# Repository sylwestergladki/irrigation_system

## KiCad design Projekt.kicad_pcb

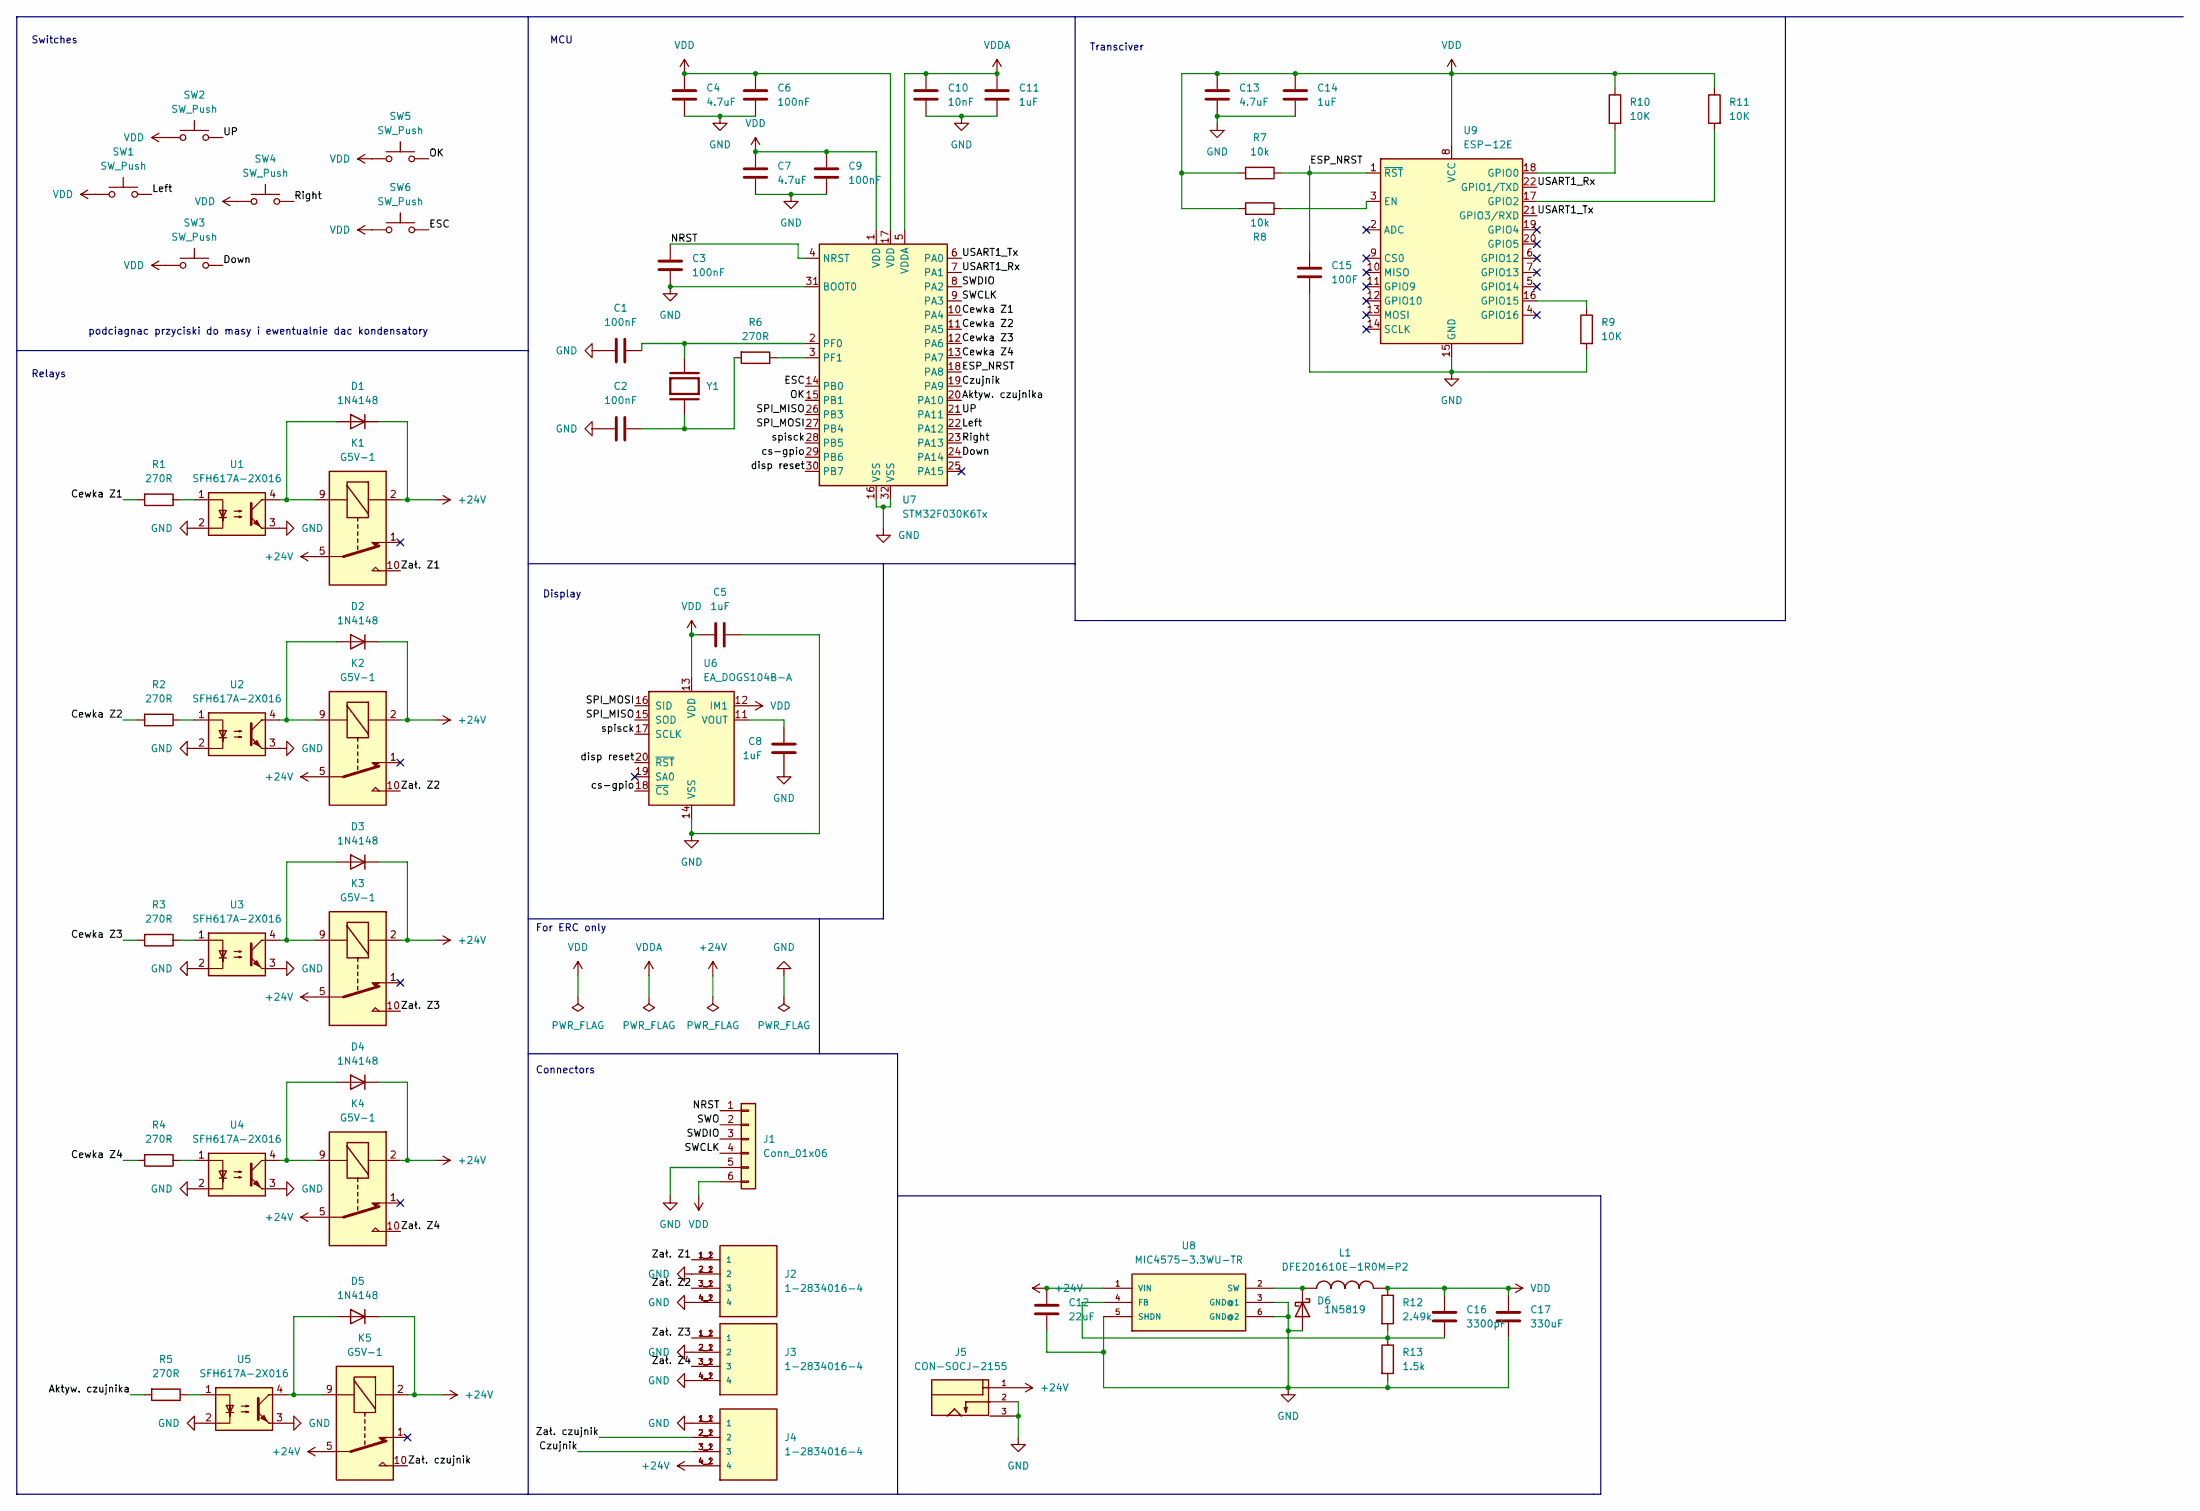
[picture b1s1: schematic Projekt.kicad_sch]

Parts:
C1, C2, C3, C6, C9: 100nF; C_0603_1608Metric
C4, C7, C13: 4.7uF; C_0603_1608Metric
C5, C8, C11, C14: 1uF; C_0603_1608Metric
C10: 10nF; C_0603_1608Metric
C12: 22uF; C_0603_1608Metric
C15: 100F; C_0603_1608Metric
C16: 3300pF; C_0603_1608Metric
C17: 330uF; C_0603_1608Metric
D1, D2, D3, D4, D5: 1N4148; D_DO-35_SOD27_P7.62mm_Horizontal
D6: 1N5819; D_DO-41_SOD81_P10.16mm_Horizontal
J1: Conn_01x06; Molex_PicoBlade_53047-0610_1x06_P1.25mm_Vertical
J2, J3, J4: 1-2834016-4; TE_1-2834016-4
J5: CON-SOCJ-2155; GRAVITECH_CON-SOCJ-2155; PARTREV NA
K1, K2, K3, K4, K5: G5V-1; Relay_SPDT_Omron_G5V-1
L1: DFE201610E-1R0M=P2; INDC2016X100N
R1, R2, R3, R4, R5, R6: 270R; R_0603_1608Metric_Pad0.98x0.95mm_HandSolder
R7, R8: 10k; R_0603_1608Metric_Pad0.98x0.95mm_HandSolder
R9, R10, R11: 10K; R_0603_1608Metric_Pad0.98x0.95mm_HandSolder
R12: 2.49k; R_0603_1608Metric_Pad0.98x0.95mm_HandSolder
R13: 1.5k; R_0603_1608Metric_Pad0.98x0.95mm_HandSolder
SW1, SW2, SW3, SW4, SW5, SW6: SW_Push; SW_Push_SPST_NO_Alps_SKRK
U1, U2, U3, U4, U5: SFH617A-2X016; DIP-4_W10.16mm
U6: EA_DOGS104B-A; EA_DOGS104X-A
U7: STM32F030K6Tx; LQFP-32_7x7mm_P0.8mm
U8: MIC4575-3.3WU-TR; TO170P1524X460-6N
U9: ESP-12E
Y1: ABM3-8.000MHZ-D2Y-T; XTAL_ABM3-8.000MHZ-D2Y-T; PARTREV 4/25/2022

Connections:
+24V: C12.1, D1.1 (K), D2.1 (K), D3.1 (K), D4.1 (K), D5.1 (K), J4.4_1 (4), J4.4_2 (4), J5.1, K1.2, K1.5, K1.6, K2.2, K2.5, K2.6, K3.2, K3.5, K3.6, K4.2, K4.5, K4.6, K5.2, K5.5, K5.6, U8.1 (VIN)
/Aktyw. czujnika: R5.2, U7.20 (PA10)
/Cewka Z1: R1.2, U7.10 (PA4)
/Cewka Z2: R2.2, U7.11 (PA5)
/Cewka Z3: R3.2, U7.12 (PA6)
/Cewka Z4: R4.2, U7.13 (PA7)
/Czujnik: J4.3_1 (3), J4.3_2 (3), U7.19 (PA9)
/Down: SW3.2, U7.24 (PA14)
/ESC: SW6.2, U7.14 (PB0)
/ESP_NRST: C15.1, R7.1, U7.18 (PA8), U9.1 (~RST)
/Left: SW1.2, U7.22 (PA12)
/NRST: C3.1, J1.1, U7.4 (NRST)
/OK: SW5.2, U7.15 (PB1)
/Right: SW4.2, U7.23 (PA13)
/SPI_MISO: U6.15 (SOD), U7.26 (PB3)
/SPI_MOSI: U6.16 (SID), U7.27 (PB4)
/SWCLK: J1.4, U7.9 (PA3)
/SWDIO: J1.3, U7.8 (PA2)
/SWO: J1.2
/UP: SW2.2, U7.21 (PA11)
/USART1_Rx: U7.7 (PA1), U9.22 (GPIO1/TXD)
/USART1_Tx: U7.6 (PA0), U9.21 (GPIO3/RXD)
/Zał. Z1: J2.1_1 (1), J2.1_2 (1), K1.10
/Zał. Z2: J2.3_1 (3), J2.3_2 (3), K2.10
/Zał. Z3: J3.1_1 (1), J3.1_2 (1), K3.10
/Zał. Z4: J3.3_1 (3), J3.3_2 (3), K4.10
/Zał. czujnik: J4.2_1 (2), J4.2_2 (2), K5.10
/cs-gpio: U6.18 (~CS), U7.29 (PB6)
/disp reset: U6.20 (~RST), U7.30 (PB7)
/spisck: U6.17 (SCLK), U7.28 (PB5)
GND: C1.2, C2.2, C3.2, C4.2, C5.1, C6.2, C7.2, C8.1, C9.2, C10.2, C11.2, C12.2, C13.2, C14.2, C15.2, C17.2, D6.2 (A), J1.5, J2.2_1 (2), J2.2_2 (2), J2.4_1 (4), J2.4_2 (4), J3.2_1 (2), J3.2_2 (2), J3.4_1 (4), J3.4_2 (4), J4.1_1 (1), J4.1_2 (1), J5.2, J5.3, R9.2, R13.2, U1.2, U1.3, U2.2, U2.3, U3.2, U3.3, U4.2, U4.3, U5.2, U5.3, U6.14 (VSS), U7.16 (VSS), U7.31 (BOOT0), U7.32 (VSS), U8.3 (GND@1), U8.5 (SHDN), U8.6 (GND@2), U9.15 (GND)
unnamed: C1.1, U7.2 (PF0), Y1.2
unnamed: C2.1, R6.2, Y1.1
unnamed: C8.2, U6.11 (VOUT)
unnamed: C16.2, R12.2, R13.1, U8.4 (FB)
unnamed: D1.2 (A), K1.9, U1.4
unnamed: D2.2 (A), K2.9, U2.4
unnamed: D3.2 (A), K3.9, U3.4
unnamed: D4.2 (A), K4.9, U4.4
unnamed: D5.2 (A), K5.9, U5.4
unnamed: D6.1 (K), L1.1, U8.2 (SW)
unnamed: R1.1, U1.1
unnamed: R2.1, U2.1
unnamed: R3.1, U3.1
unnamed: R4.1, U4.1
unnamed: R5.1, U5.1
unnamed: R6.1, U7.3 (PF1)
unnamed: R8.1, U9.3 (EN)
unnamed: R9.1, U9.16 (GPIO15)
unnamed: R10.2, U9.18 (GPIO0)
unnamed: R11.2, U9.17 (GPIO2)
VDD: C4.1, C5.2, C6.1, C7.1, C9.1, C13.1, C14.1, C16.1, C17.1, J1.6, L1.2, R7.2, R8.2, R10.1, R11.1, R12.1, SW1.1, SW2.1, SW3.1, SW4.1, SW5.1, SW6.1, U6.12 (IM1), U6.13 (VDD), U7.1 (VDD), U7.17 (VDD), U9.8 (VCC)
VDDA: C10.1, C11.1, U7.5 (VDDA)

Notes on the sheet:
Transciver
Display
Connectors
podciagnac przyciski do masy i ewentualnie dac kondensatory
Relays
Switches
For ERC only
MCU

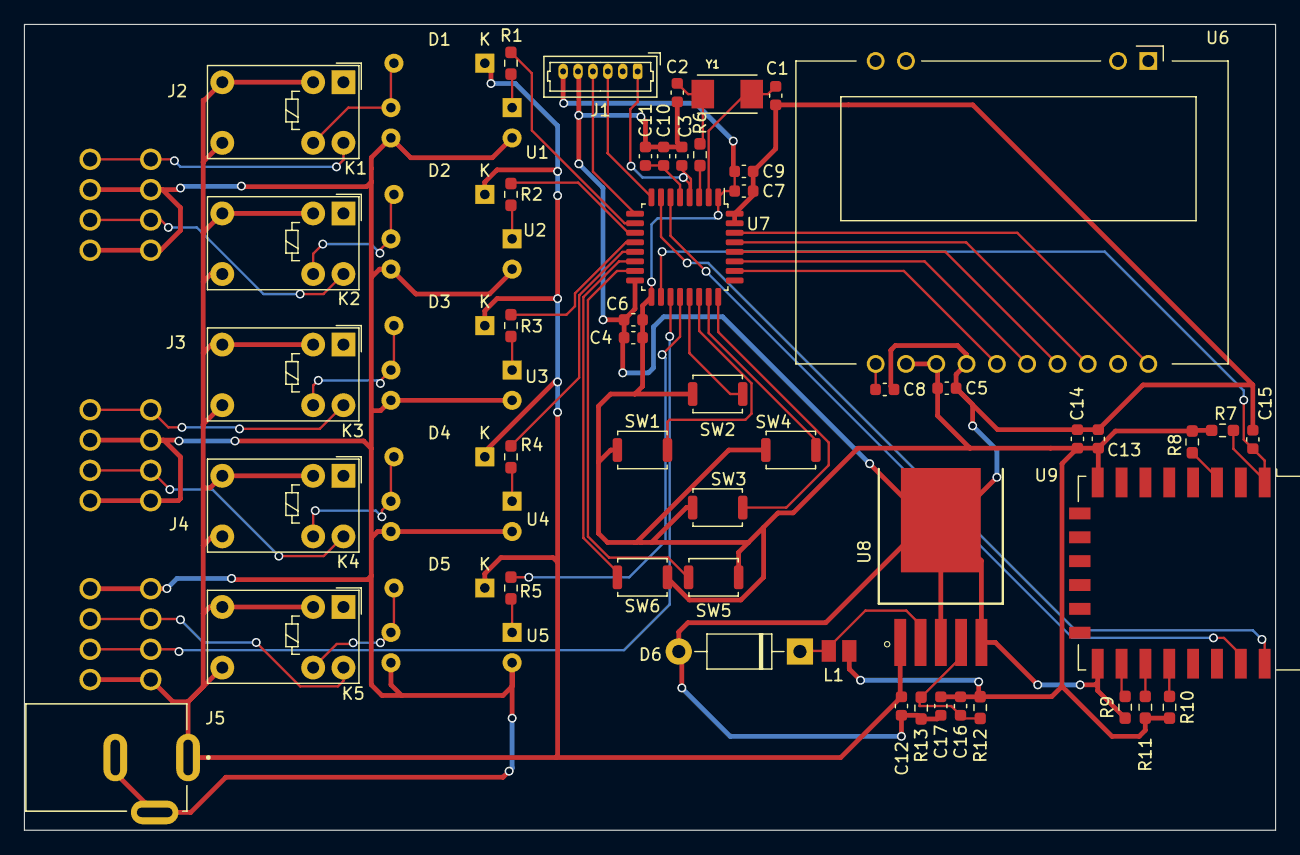
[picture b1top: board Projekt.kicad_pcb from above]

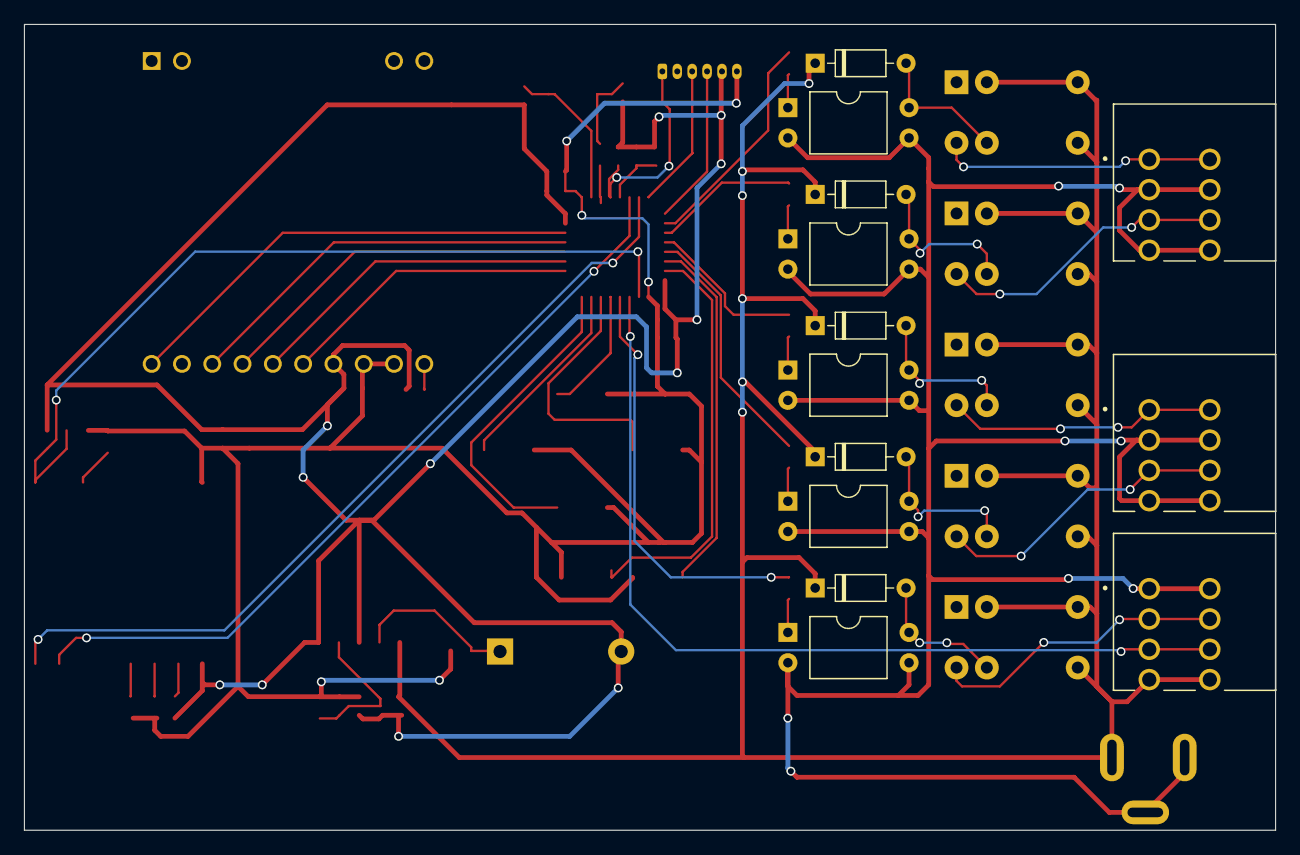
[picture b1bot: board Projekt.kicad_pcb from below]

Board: 2 copper layers, 104.9 x 67.6 mm, 63 parts (13 on the bottom side), 52 nets.

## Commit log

2022-10-19 Pierwszy commit
2022-10-19 Dodanie pustego readme
2022-10-19 dodanie przetwornicy 24/3,3V Dodanie STM32 Dodanie polaczen przy przekaznikach
2022-10-26 - Zmieniłem przekazniki z 3,3v na 24v - Dolozylem sterowanie przekaznikiem przez transoptor - Dodalem zlacza 4 stykowe do elektrozaworow i czujnika - Dodalem gniazdo jack zasilania 24VDC
2022-10-26 - Dodalem 6 przyciskow NO - Dodalem folder z plikami od podzespolow ktore uzylem + plik exela z wypisanymi komponentami, ich cenami i linkami do sklepu
2022-11-03 - zmiany i udoskonalenie pliku exel z podzespolami - calkowite przerobienie schematu zgodnie z sztuka z filmu nr2 - zmiana procka i podlaczenie go - zmiana transcivera i podlaczenie go
2022-11-04 Dodanie wyswietlacza wizualne poprawki
2022-11-05 Dodanie komentarzy po spotkaniu z prowadzącym
2022-11-28 - drobne poprawki wizualne w schemacie - część wstępnego rozłożenia elementów
2022-12-11 Rozłożenie footprintów na schemacie
2023-01-02 test1 polaczen
2023-01-04 Połączenia v2
2023-01-04 Połączenia v2.1
